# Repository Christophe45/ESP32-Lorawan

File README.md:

# ESP32-Lorawan
ESP32 Lorawan beehive connected

This project is to make a connected hive that can control the weight, the internal and external temperature of the hive as well as the humidity. Data recovery is done with a Lora RFM95 module and reception of this data through a gateway connected to TTN. The data received on TTN is then sent to Node-red and sent back to Blynk's servers.

The schematic of the Lorawan is:

PCB 3D :

New version on test with a GPS module NOE6NV2 and an accelerometer MPU6050 used for alarm detection when the hive is moved.

schematic:

PCB 3D :

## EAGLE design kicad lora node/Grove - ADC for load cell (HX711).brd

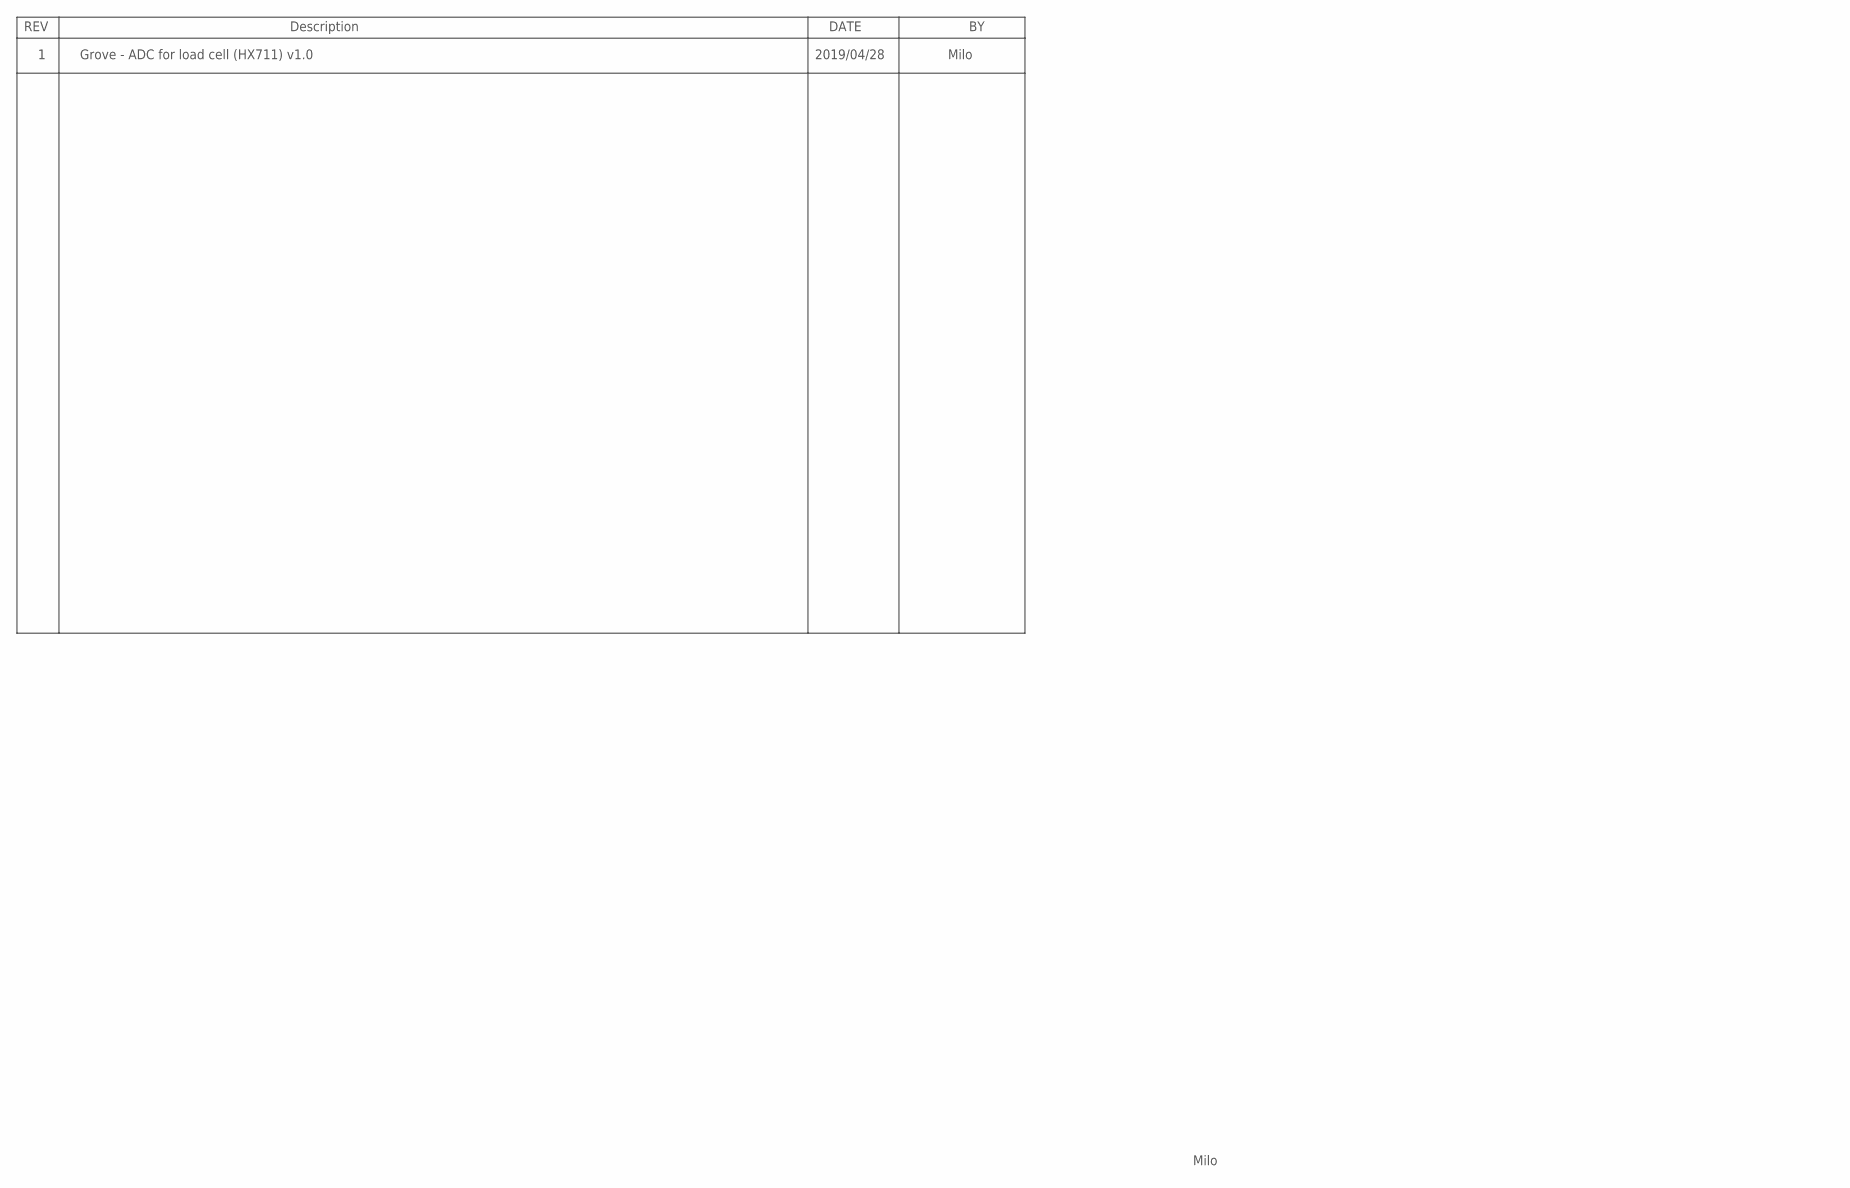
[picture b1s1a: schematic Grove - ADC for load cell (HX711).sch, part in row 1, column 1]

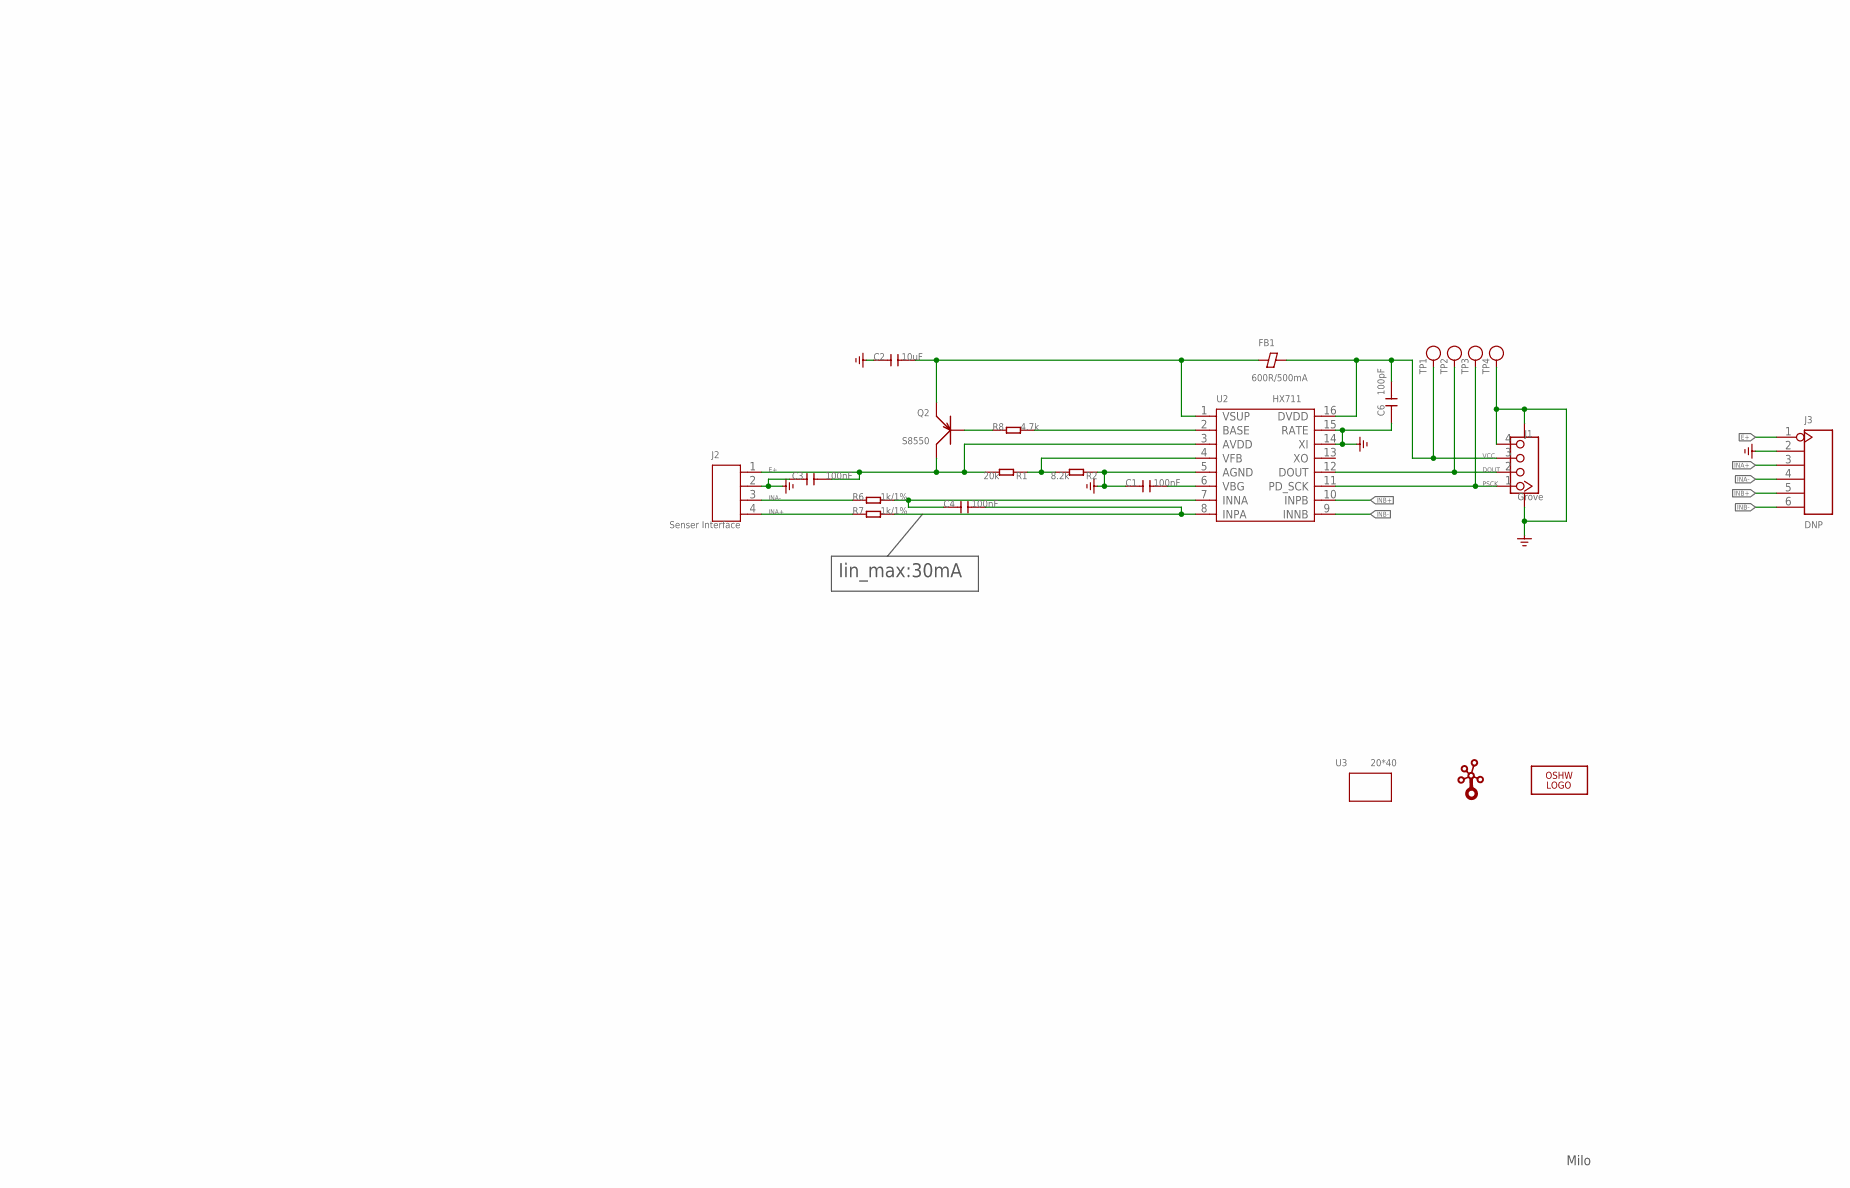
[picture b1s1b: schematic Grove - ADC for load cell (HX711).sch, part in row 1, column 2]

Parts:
C1, C3, C4: 100nF; C0603
C2: 10uF; C0603
C6: 100pF; C0603
FB1: 600R/500mA; F0805
J1: Grove; HW4-SMD-2.0
J2: Senser Interface; H4-3.5-14.0X7.0MM
J3: DNP; H6-2.54
LOGO1: LOGO-OSHW-FILLX0150-NT; OSHW_FILLX150_NOTEXT
Q2: S8550; SOT-23
R1: 20k; R0603
R2: 8.2k; R0603
R6, R7: 1k/1%; R0603
R8: 4.7k; R0603
TP1, TP2, TP3, TP4: DNP; TP-D45MIL
U2: HX711; SOIC16-1.27-10X3.9MM
U3: 20*40; GROVE-1*2-TEST-PLATFORM-TOP
U$2: LOGO-GROVE; GROVE-SILK-BIG

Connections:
DOUT: J1.2, TP2.T, U2.12 (DOUT)
E+: C3.1, J2.1, J3.1, Q2.3 (C), R1.2, U2.3 (AVDD)
GND: C1.1, C2.1, C3.2, C6.1, J1.4, J1.SS1, J1.SS2, J2.2, J3.2, R2.1, TP4.T, U2.5 (AGND), U2.14 (XI), U2.15 (RATE)
INA+: J2.4, J3.3, R7.1
INA-: J2.3, J3.4, R6.1
INB+: J3.5, U2.10 (INPB)
INB-: J3.6, U2.9 (INNB)
unnamed: R1.1, R2.2, U2.4 (VFB)
unnamed: Q2.1 (B), R8.1
unnamed: C2.2, FB1.1, Q2.2 (E), U2.1 (VSUP)
unnamed: C1.2, U2.6 (VBG)
unnamed: R8.2, U2.2 (BASE)
unnamed: C4.2, R7.2, U2.8 (INPA)
unnamed: C4.1, R6.2, U2.7 (INNA)
PSCK: J1.1, TP3.T, U2.11 (PD_SCK)
VCC: C6.2, FB1.2, J1.3, TP1.T, U2.16 (DVDD)

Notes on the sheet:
Grove - ADC for load cell (HX711) v1.0
2019/04/28
Milo
Iin_max:30mA

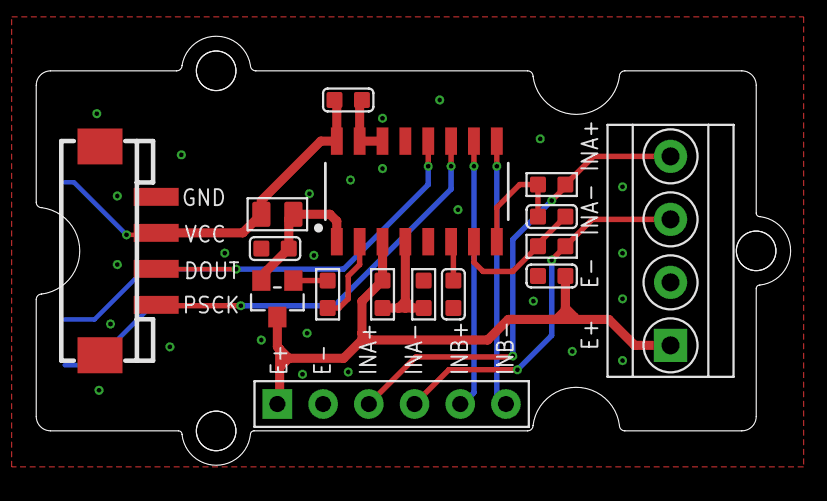
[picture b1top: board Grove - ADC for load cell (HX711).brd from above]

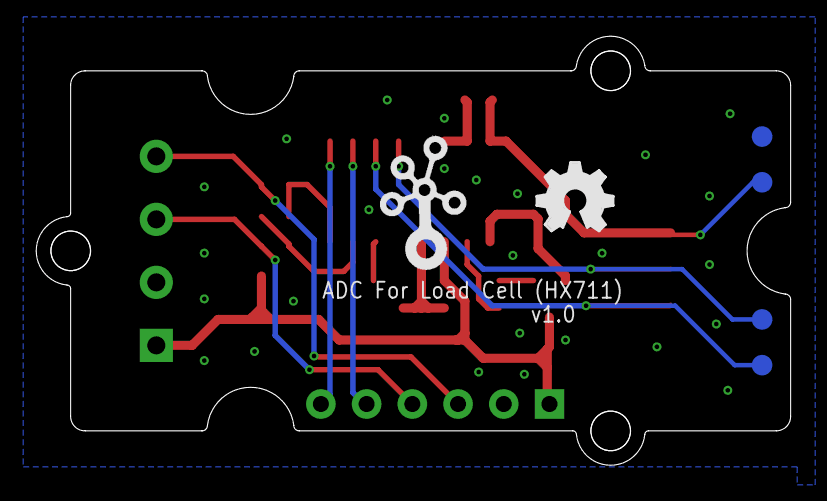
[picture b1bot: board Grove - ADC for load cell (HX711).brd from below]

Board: 2 copper layers, 41.9 x 23.8 mm, 23 parts (6 on the bottom side), 16 nets.

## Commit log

2020-01-17 Create pictures
2020-01-17 first commit1
2020-01-20 Remove duplicated directory
2020-12-01 Create libraries

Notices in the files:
parts and their libraries:
moudle-new: CC-BY-SA
